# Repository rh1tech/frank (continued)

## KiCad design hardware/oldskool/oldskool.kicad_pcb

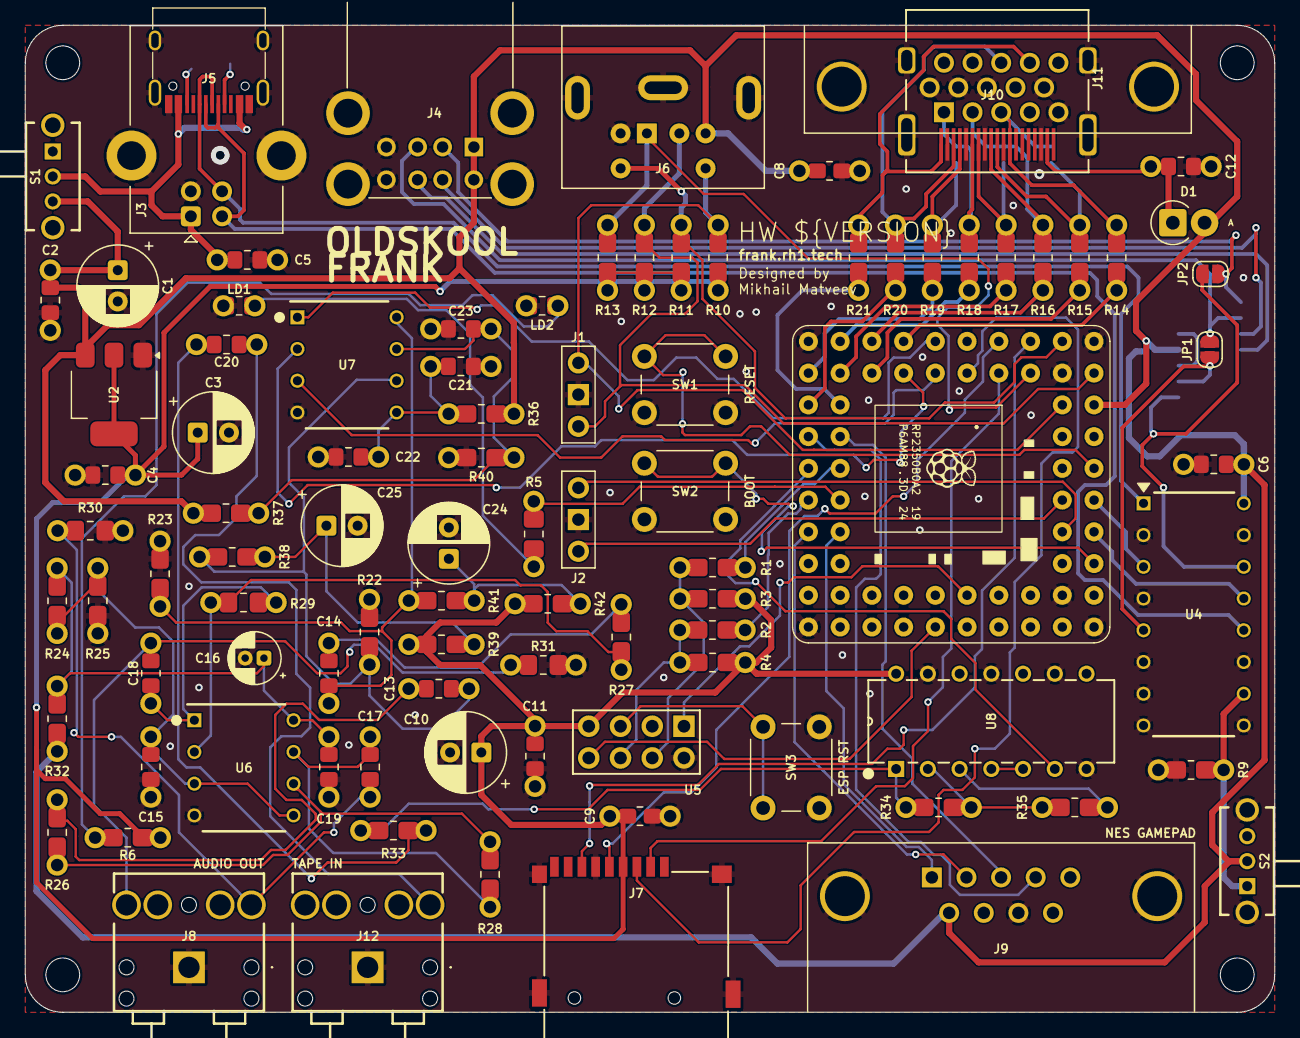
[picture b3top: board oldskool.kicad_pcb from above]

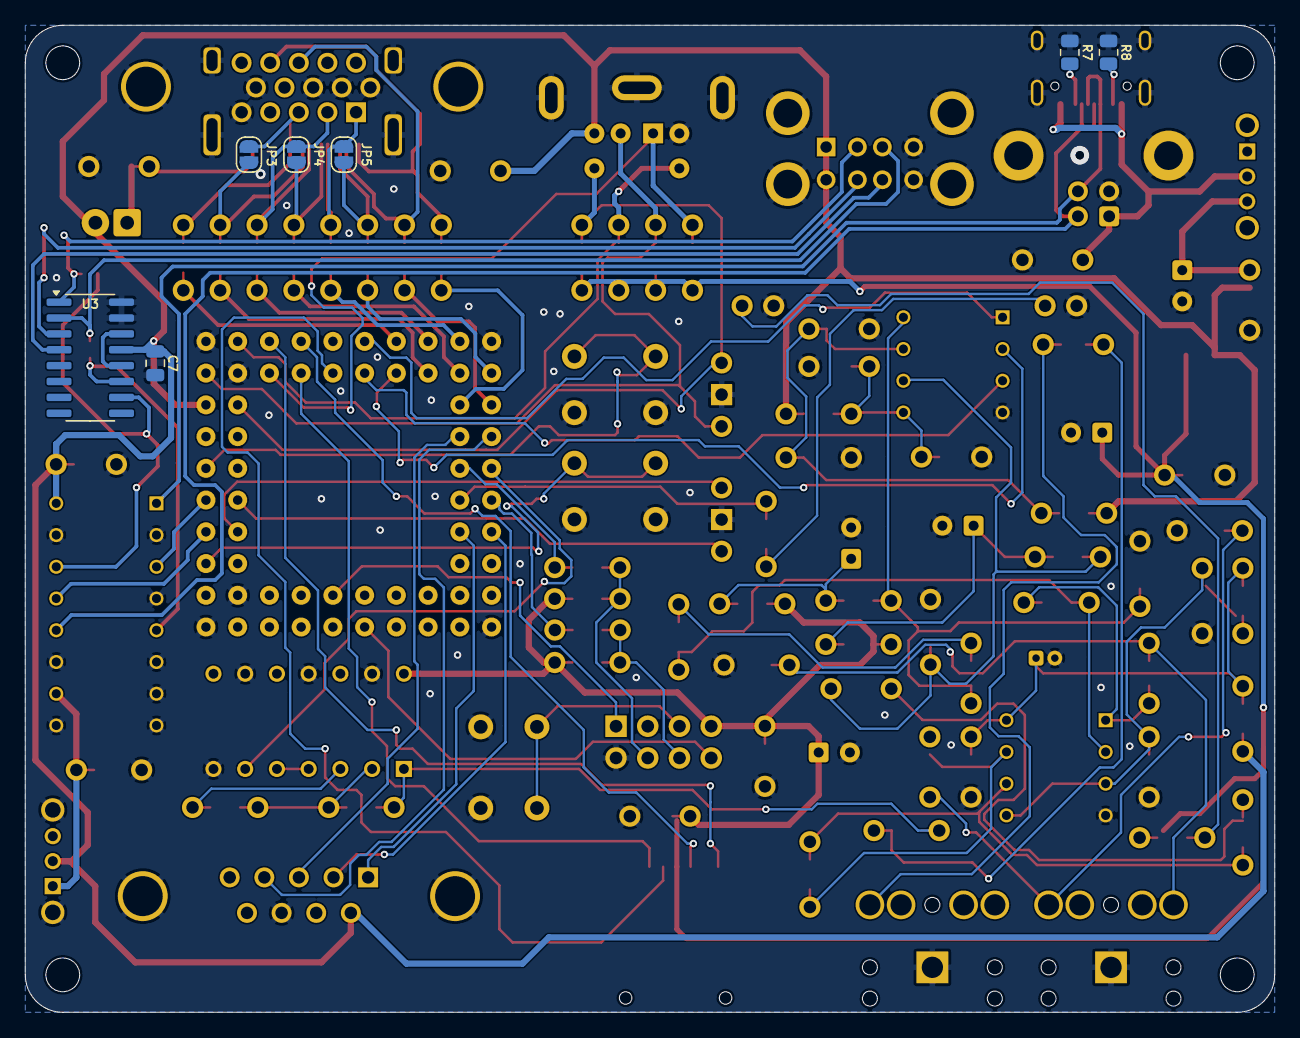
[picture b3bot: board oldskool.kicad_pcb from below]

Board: 2 copper layers, 100.0 x 79.0 mm, 104 parts (7 on the bottom side), 87 nets.

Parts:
C1, C3, C10, C24, C25: 100u; C_Radial_D6.3mm_P2.50mm
C2, C4, C6, C8, C9, C11, C12, C19, C20, C22: 100n; Combined_0805_CR
C5, C13, C14, C15, C17, C18, C21, C23: 10u; Combined_0805_CR
C7: 4.7u; C_0805_2012Metric
C16: 10u; CP_Radial_D4.0mm_P1.50mm
D1: 1N5819; D_SOD81_P2.54mm_Vertical_AnodeUp
H1, H2, H3, H4: Hole 2.7mm; MountingHole_2.7mm
J1: UART; PinSocket_1x03_P2.54mm_Vertical
J2: Debug; PinSocket_1x03_P2.54mm_Vertical
J3: USB_B; USB_B_Horizontal
J4: SS-52100-004; USB_A_Stacked
J5: USB4215-03-A; USB_C_Receptacle
J6: MDC-036; MiniDIN_6pin_Female
J7: 104031-0811; MicroSD_SMD_Long
J8: SJ1-3525N Green; AudioJack_3.5mm_SJ1-3525N_Green
J9: D-SUB 9 Male; DSUB-9_Male_TopMount
J10: DC3RX19JA2; HDMI_Female
J11: D-SUB 15 Female; DSUB-15_Female
J12: SJ1-3525N Red; AudioJack_3.5mm_SJ1-3525N_Red
JP1, JP2, JP3, JP4, JP5: Jumper (Solder); SolderJumper_2Pin
LD1: Blue; Combined_0805_LED
LD2: Green; Combined_0805_LED
R1, R2, R5, R6, R10, R11, R12, R13: 1K; Combined_0805_RE
R3, R4, R9, R24, R25, R26, R27, R40: 10K; Combined_0805_RE
R7, R8: 5.1K; R_0805_2012Metric
R14, R15, R16, R17, R18, R19, R20, R21: 220R; Combined_0805_RE
R22, R23: 2.2K; Combined_0805_RE
R28, R29: 47K; Combined_0805_RE
R30, R31: 20K; Combined_0805_RE
R32, R36, R39, R42: 100R; Combined_0805_RE
R33: 4.7K; Combined_0805_RE
R34, R35: 100K; Combined_0805_RE
R37: 51K; Combined_0805_RE
R38, R41: 470R; Combined_0805_RE
S1, S2: SK12D07VG3NS; Switch_Slide_SK12D07VG3NS
SW1: Reset; SW_PUSH_6mm_H5mm
SW2: Boot; SW_PUSH_6mm_H5mm
SW3: ESP01 Reset; SW_PUSH_6mm_H5mm
U1: Pimoroni PGA2350; PGA2350
U2: AMS1117-3.3; SOT-223-3_TabPin2
U3: MW7211A; SOP-16_3.9x9.9mm_P1.27mm
U4: 74HC4052; 74HC4052N
U5: ESP-01v090; ESP-01S
U6: LM358; DIP-8_W7.94mm_P2.54mm
U7: TDA1545A; DIP-8_W7.94mm_P2.54mm
U8: CD4069UBE

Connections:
+3V3: C3.1, C4.2, C9.2, C10.1, C11.2, J7.4 (VDD), R3.2, R4.2, R6.2, R10.2, R11.2, R12.2, R13.2, R39.1, R42.1, U2.2 (VO), U5.7 (VCC), U8.14 (VDD)
/Audio/AMP_OUTL: C17.2, J8.2 (TIP), R30.2
/Audio/AMP_OUTR: C18.2, J8.3 (RING), R31.2
/Audio/TDA_L: C13.1, R22.1, R38.2, U7.6 (IOL)
/Audio/TDA_R: C14.1, R23.1, R41.1, U7.8 (IOR)
/CDDAT3/GP5: J7.2 (DAT3/CD), U1.5 (GP5)
/CLKN/GP12: R14.2, U1.12 (GP12)
/CLKP/GP13: R15.2, U1.13 (GP13)
/CLK/GP6: J7.5 (CLK), U1.6 (GP6)
/CMD/GP7: J7.3 (CMD), U1.7 (GP7)
/D0N/GP14: R16.2, U1.14 (GP14)
/D0P/GP15: R17.2, U1.15 (GP15)
/D1N/GP16: R18.2, U1.16 (GP16)
/D1P/GP17: R19.2, U1.17 (GP17)
/D2N/GP18: R20.2, U1.19 (GP18)
/D2P/GP19: R21.2, U1.20 (GP19)
/DAT0/GP4: J7.7 (DAT0), U1.4 (GP4)
/DATA1/GP26: J9.2, U1.27 (GP26)
/DATA2/GP27: J9.1, U1.28 (GP27)
/DM: U1.53 (USB_DM), U4.13 (1Z)
/DP: U1.54 (USB_DP), U4.3 (2Z)
/EGP0/GP24: R2.2, U1.25 (GP24)
/EGP2/GP23: R1.2, U1.24 (GP23)
/ESP01S/GPIO0: R2.1, R4.1, U5.6 (GPIO0)
/ESP01S/GPIO2: R1.1, R3.1, U5.4 (GPIO2)
/J3/GP21: J9.3, U1.22 (GP21)
/J4/GP20: J9.4, U1.21 (GP20)
/KB_CLK/GP2: J6.5, R11.1, U1.2 (GP2)
/KB_DATA/GP3: J6.1, R13.1, U1.3 (GP3)
/LOAD_IN/GP22: U1.23 (GP22), U8.6 (I=*C)
/MS_CLK/GP0: J1.1, J6.6, R10.1, U1.61 (GP0)
/MS_DATA/GP1: J1.3, J6.2, R12.1, U1.62 (GP1)
/PGA2350/BOOTSEL: SW2.1, U1.51 (BOOTSEL)
/PGA2350/RUN: SW1.1, U1.56 (RUN)
/PGA2350/SWCLK: J2.3, U1.55 (SWCLK)
/PGA2350/SWDIO: J2.1, U1.52 (SWDIO)
/RX/GP38: U1.40 (GP38), U5.8 (URXD)
/TDA_DATA/GP9: U1.9 (GP9), U7.3 (DATA)
/TDA_LRCK/GP11: U1.11 (GP11), U7.2 (WS)
/TDA_SCLK/GP10: U1.10 (GP10), U7.1 (BCK)
/TX/GP39: U1.41 (GP39), U5.1 (UTXD)
/Tape In/TAPE: C20.2, J12.2 (TIP)
/USB/DI+: J3.3 (D+), J5.6 (DP1), J5.8 (DP2), U4.1 (2Y0)
/USB/DI-: J3.2 (D-), J5.5 (DN2), J5.7 (DN1), U4.12 (1Y0)
/USB/DS+: JP1.1 (A), U3.11 (DPU), U4.5 (2Y1)
/USB/DS-: JP2.1 (A), U3.10 (DMU), U4.14 (1Y1)
/USB/DU1+: J4.3 (D1+), JP1.2 (B), U3.2 (DP0)
/USB/DU1-: J4.2 (D1-), JP2.2 (B), U3.1 (DM0)
/USB/DU2+: J4.7 (D2+), U3.4 (DP1)
/USB/DU2-: J4.6 (D2-), U3.3 (DM1)
/USB/VBUS_IN: C5.1, J3.1 (VBUS), J5.2 (VBUS), J5.11 (VBUS), S1.2
/Video Out/VGA_B: J10.12 (CLKN), J11.3, JP3.1 (A), R14.1
/Video Out/VGA_BH: J10.10 (CLKP), JP3.2 (B), R15.1
/Video Out/VGA_G: J10.9 (D0N), J11.2, JP4.1 (A), R16.1
/Video Out/VGA_GH: J10.7 (D0P), JP4.2 (B), R17.1
/Video Out/VGA_HS: J10.3 (D2N), J11.13, R20.1
/Video Out/VGA_R: J10.6 (D1N), J11.1, JP5.1 (A), R18.1
/Video Out/VGA_RH: J10.4 (D1P), JP5.2 (B), R19.1
/Video Out/VGA_VS: J10.1 (D2P), J11.14, R21.1
GND: C1.2, C2.1, C3.2, C4.1, C5.2, C6.1, C7.2, C8.2, C9.1, C10.2, C11.1, C12.2, C15.1, C16.2, C19.1, C21.2, C22.2, C23.1, C24.2, C25.2, J1.2, J2.2, J3.4 (GND), J3.SH (Shield), J4.4 (GND1), J4.8 (GND2), J4.SH (Shield), J5.1 (GND), J5.12 (GND), J5.13 (SHIELD), J6.3, J7.6 (VSS), J8.1 (SLEEVE), J9.8, J10.2 (G_D2), J10.5 (G_D1), J10.8 (G_D0), J10.11 (G_CLK), J10.17 (G_DDC/CEC), J10.20 (SHIELD1), J10.21 (SHIELD2), J10.22 (SHIELD3), J10.23 (SHIELD4), J11.0, J11.5, J11.6, J11.7, J11.8, J11.10, J12.1 (SLEEVE), LD1.1 (K), LD2.1 (K), R7.1, R8.1, R9.1, R22.2, R23.2, R25.1, R30.1, R31.1, R40.1, S2.4 (MH1), S2.5 (MH2), SW1.2, SW2.2, SW3.2, U1.1 (GND), U1.18 (GND), U1.33 (GND), U1.48 (GND), U2.1 (GND), U3.15 (GND), U3.16 (GND), U4.2 (2Y2), U4.4 (2Y3), U4.6 (~E), U4.7 (VEE), U4.8 (GND), U4.9 (S1), U4.11 (1Y3), U4.15 (1Y2), U5.2 (GND), U6.4 (V-), U7.4 (GND), U8.7 (VSS), U8.9 (D14), U8.11 (E), U8.13 (F)
GP25: R5.2, U1.26 (GP25)
unnamed: C13.2, R26.2
unnamed: C14.2, R27.2
unnamed: C17.1, R28.1, U6.7
unnamed: C18.1, R29.1, U6.1
unnamed: C20.1, R33.2
unnamed: C24.1, R41.2, R42.2
unnamed: C25.1, R38.1, R39.2
unnamed: C12.1, D1.1 (K), J10.18 (+5V)
unnamed: J5.4 (CC1), R7.2
unnamed: J5.10 (CC2), R8.2
unnamed: LD1.2 (A), R5.1
unnamed: LD2.2 (A), R6.1
unnamed: U3.12 (VD33), U3.14 (VD3)
unnamed: R9.2, S2.1, U4.10 (S0)
unnamed: SW3.1, U5.5 (RST)
unnamed: C15.2, R24.1, R25.2, U6.3 (+), U6.5 (+)
unnamed: R27.1, R29.2, U6.2 (-)
unnamed: R26.1, R28.2, U6.6 (-)
unnamed: C16.1, C19.2, R24.2, R32.2, U6.8 (V+)
unnamed: C23.2, R37.2, R40.2, U7.7 (IREF)
unnamed: C21.1, C22.1, R36.1, U7.5 (VDD)
unnamed: R33.1, R34.2, U8.1 (A)
unnamed: R35.1, U8.3 (B)
unnamed: U8.4 (H=*B), U8.5 (C)
unnamed: R34.1, R35.2, U8.2 (G-*A)
VBUS: C1.1, C2.2, C6.2, C7.1, C8.1, D1.2 (A), J4.1 (VBUS1), J4.5 (VBUS2), J6.4, J9.6, R32.1, R36.2, R37.1, S1.3, S2.2, U1.60 (VBUS), U2.3 (VI), U3.13 (VDD5), U4.16 (VCC)

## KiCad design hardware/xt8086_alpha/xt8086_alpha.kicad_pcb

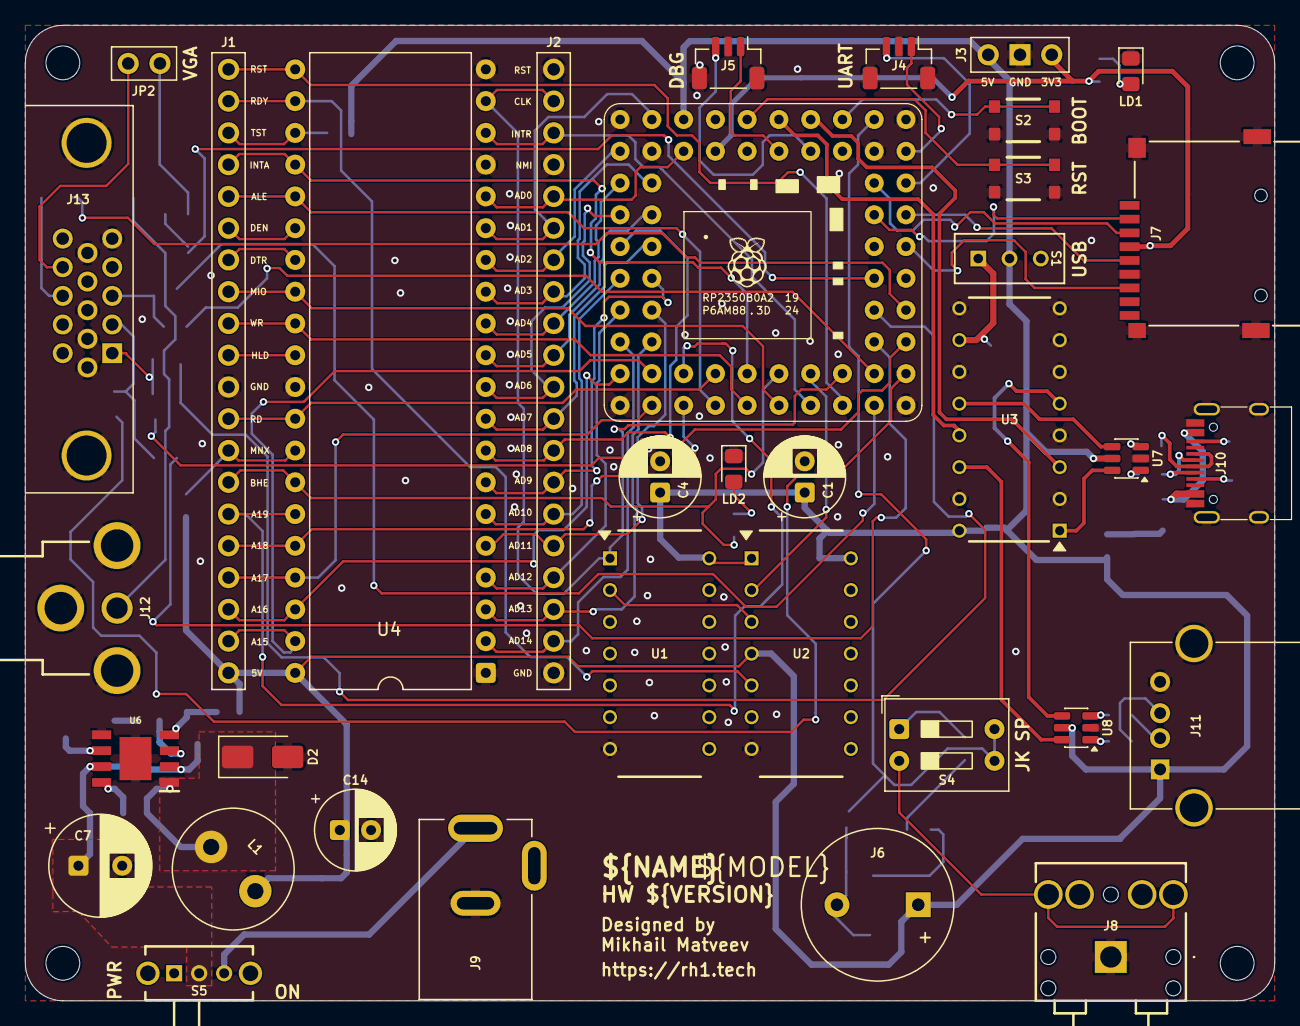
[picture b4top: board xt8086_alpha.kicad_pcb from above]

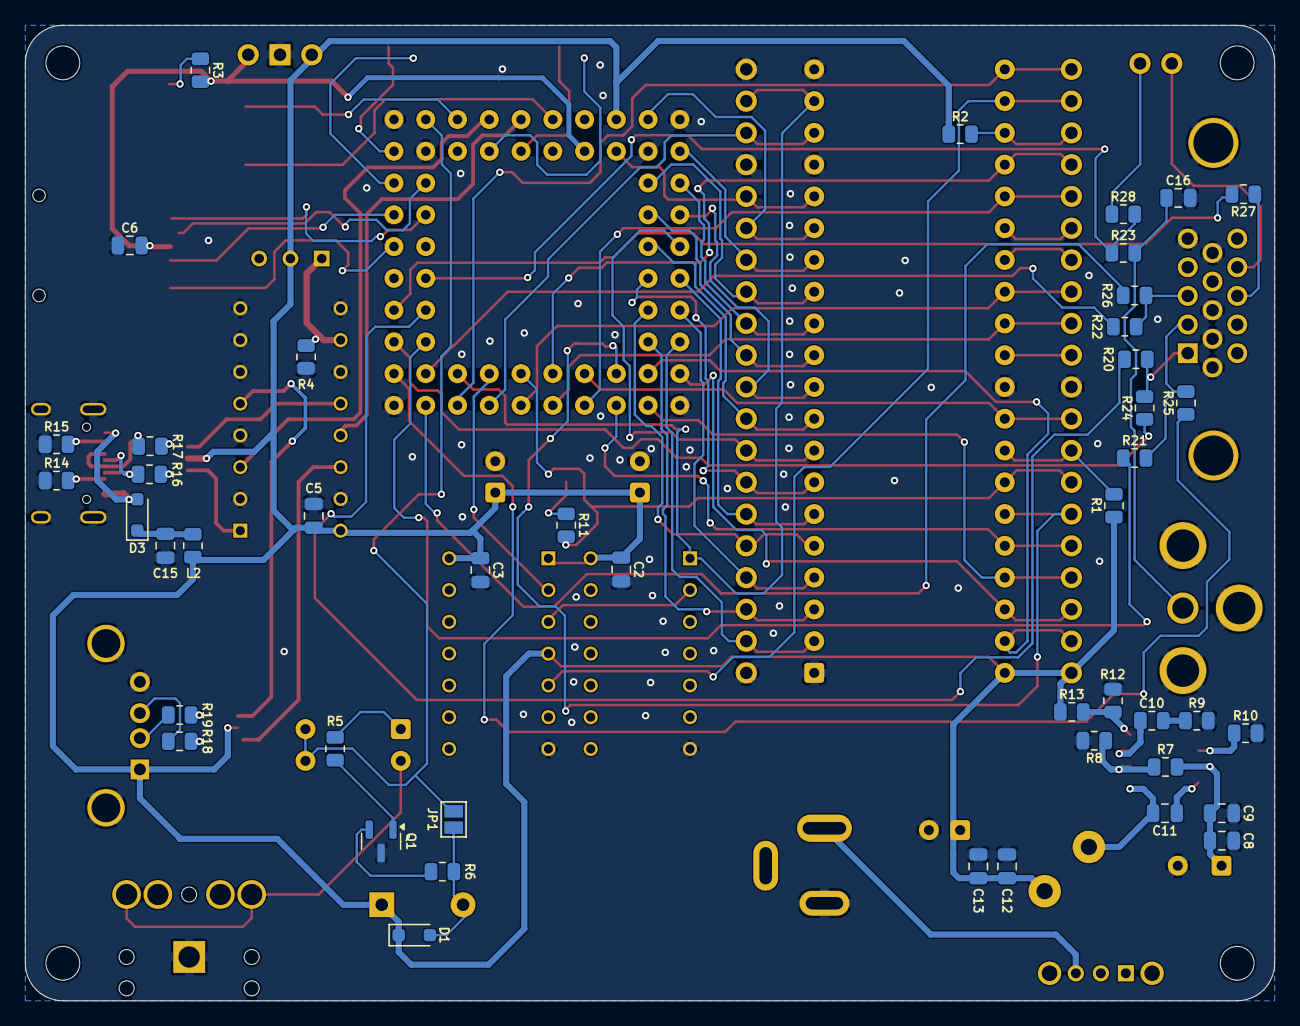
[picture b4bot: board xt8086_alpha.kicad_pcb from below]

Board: 2 copper layers, 99.9 x 78.0 mm, 84 parts (45 on the bottom side), 101 nets.

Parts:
C1, C4: 100u; CP_Radial_D6.3mm_P2.50mm
C2, C3, C5, C6, C9, C11, C12, C15: 100n; C_0805_2012Metric
C7: 680u; C_Radial_D8.0mm_P3.50mm
C8, C13: 10u; C_0805_2012Metric
C10: 150pF; R_0805_2012Metric
C14: 220u; C_Radial_D6.3mm_P2.50mm
C16: 470pF; C_0805_2012Metric
D1: 1N4148; D_SOD-323
D2: 1N5822; D_SMA
D3: 1N5819WS; D_SOD-323
H1, H2, H3, H4: Hole 2.7mm; MountingHole_2.7mm
J1: 8086_Pins_Left; PinSocket_1x20_P2.54mm_Vertical
J2: 8086_Pins_Right; PinSocket_1x20_P2.54mm_Vertical
J3: PWR; PinHeader_1x03_P2.54mm_Vertical
J4: UART; JST_SH_1x03_P1.00mm_Vertical
J5: Debug; JST_SH_1x03_P1.00mm_Vertical
J6: Buzzer; Buzzer_12x8.5RM6.5
J7: 104031-0811; MicroSD_SMD_Long
J8: SJ1-3525N; AudioJack_3.5mm_SJ1-3525N
J9: DC-005-5A-2.0; BarrelJack_DC-005
J10: USB4215-03-A; USB_C_Receptacle
J11: 676430910; USB_A_Single
J12: RCA-103; BarrelJack_RCJ-012
J13: D-SUB 15 Female; DSUB-15_Female
JP1: Direct; SolderJumper-2_P1.3mm_Open_Pad1.0x1.5mm
JP2: VGA VS; PinHeader_1x02_P2.54mm
L1: 22uH; L_Radial_D9.5mm_P5.00mm_Fastron_07HVP
L2: 330R; R_0805_2012Metric
LD1: Green; LED_0805_2012Metric_Pad1.15x1.40mm_HandSolder
LD2: Red; LED_0805_2012Metric_Pad1.15x1.40mm_HandSolder
Q1: BC847; SOT-23
R1, R2, R3, R5, R11, R24, R25, R26: 1K; R_0805_2012Metric
R4: 10K; R_0805_2012Metric
R6, R16, R17, R18, R19: 22R; R_0805_2012Metric
R7, R9, R10: 100K; R_0805_2012Metric
R8: 24K; R_0805_2012Metric
R12: 8.2K; R_0805_2012Metric
R13: 43K; R_0805_2012Metric
R14, R15: 5.1K; R_0805_2012Metric
R20, R21, R22: 330R; R_0805_2012Metric
R23: 75R; R_0805_2012Metric
R27, R28: 100R; R_0805_2012Metric
S1: SS12D00; Switch_Slide_SS12D00
S2: Boot; Button_SMD_3x4x2mm
S3: Reset; Button_SMD_3x4x2mm
S4: SW_DIP_x02; SW_DIP_SPSTx02_Slide_9.78x7.26mm_W7.62mm_P2.54mm
S5: SK12D07VG3NS; Switch_Slide_SK12D07VG3NS
U1: SN74LS04; DIP-14_W7.62mm
U2: SN74LS74; DIP-14_W7.62mm
U3: 74HC4052D; 74HC4052N
U4: 8086_Min_Mode; DIP-40_W15.24mm
U5: Pimoroni PGA2350; PGA2350
U6: MP1584EN-LF-Z; SOIC-9_P1.27mm
U7, U8: USBLC6-2SC6; SOT-23-6

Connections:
+3V3: C6.2, J3.3, J7.4 (VDD), R3.2, U5.59 (3V3)
/A16/GP16: J1.18, U4.38 (A16/S3), U5.16 (GP16)
/A17/GP17: J1.17, U4.37 (A17/S4), U5.17 (GP17)
/A18/GP18: J1.16, U4.36 (A18/S5), U5.19 (GP18)
/A19/GP19: J1.15, U4.35 (A19/S6), U5.20 (GP19)
/AD0/GP0: J2.5, U4.16 (AD0), U5.61 (GP0)
/AD1/GP1: J2.6, U4.15 (AD1), U5.62 (GP1)
/AD2/GP2: J2.7, U4.14 (AD2), U5.2 (GP2)
/AD3/GP3: J2.8, U4.13 (AD3), U5.3 (GP3)
/AD4/GP4: J2.9, U4.12 (AD4), U5.4 (GP4)
/AD5/GP5: J2.10, U4.11 (AD5), U5.5 (GP5)
/AD6/GP6: J2.11, U4.10 (AD6), U5.6 (GP6)
/AD7/GP7: J2.12, U4.9 (AD7), U5.7 (GP7)
/AD8/GP8: J2.13, U4.8 (AD8), U5.8 (GP8)
/AD9/GP9: J2.14, U4.7 (AD9), U5.9 (GP9)
/AD10/GP10: J2.15, U4.6 (AD10), U5.10 (GP10)
/AD11/GP11: J2.16, U4.5 (AD11), U5.11 (GP11)
/AD12/GP12: J2.17, U4.4 (AD12), U5.12 (GP12)
/AD13/GP13: J2.18, U4.3 (AD13), U5.13 (GP13)
/AD14/GP14: J2.19, U4.2 (AD14), U5.14 (GP14)
/AD15/GP15: J1.19, U4.39 (AD15), U5.15 (GP15)
/ALE/GP20: J1.5, U4.25 (ALE), U5.21 (GP20)
/Audio/JACK_IN: J8.2 (TIP), J8.3 (RING), S4.2
/Audio/SPEAKER: JP1.2, S4.3, S4.4, U5.49 (GP46)
/Audio/SPK_IN: R5.1, S4.1
/BOOTSEL: S2.2, S2.4, U5.51 (BOOTSEL)
/CLK/GP29: J2.2, U1.1 (1A), U4.19 (CLK), U5.30 (GP29)
/DEN: J1.6, U4.26 (~DEN)
/DT/R: J1.7, U4.27 (DT/~R)
/GP27: U2.2 (D1), U5.28 (GP27)
/HLDA: J1.10, U4.30 (HLDA)
/INTA/GP23: J1.4, U4.24 (~INTA), U5.24 (GP23)
/INTR/GP26: J2.3, U4.18 (INTR), U5.27 (GP26)
/MIO/GP24: J1.8, U4.28 (M/~IO), U5.25 (GP24)
/MN/MX: J1.13, R1.2, U4.33 (MN/~MX)
/Micro SD/CDDAT3: J7.2 (DAT3/CD), U5.43 (GP41)
/Micro SD/CLK: J7.5 (CLK), U5.44 (GP42)
/Micro SD/CMD: J7.3 (CMD), U5.45 (GP43)
/Micro SD/DAT0: J7.7 (DAT0), U5.42 (GP40)
/PGA2350/DM: U3.3 (2Z), U5.53 (USB_DM)
/PGA2350/DP: U3.13 (1Z), U5.54 (USB_DP)
/PGA2350/GP30: R26.1, U5.31 (GP30)
/PGA2350/GP31: R22.1, U5.32 (GP31)
/PGA2350/GP32: R25.1, U5.34 (GP32)
/PGA2350/GP33: R21.1, U5.35 (GP33)
/PGA2350/GP34: R24.1, U5.36 (GP34)
/PGA2350/GP35: R20.1, U5.37 (GP35)
/PGA2350/GP36: R27.2, U5.38 (GP36)
/PGA2350/GP37: R23.1, R28.2, U5.39 (GP37)
/Power/VBUS_IN: C7.1, C8.1, C9.1, R7.2, S5.2, U6.7 (VIN)
/RD/GP21: J1.12, U4.32 (~RD), U5.22 (GP21)
/READY: J1.2, U2.5 (Q1), U4.22 (READY)
/RESET/GP28: J1.1, U4.21 (RESET), U5.29 (GP28)
/RUN: S3.2, S3.4, U5.56 (RUN)
/SWCLK: J5.3, U5.55 (SWCLK)
/SWDIO: J5.1, U5.52 (SWDIO)
/TEST: J1.3, R2.2, U4.23 (~TEST)
/UART0_RX: J4.3, U5.47 (GP45)
/UART0_TX: J4.1, U5.46 (GP44)
/USB/SW: R4.2, S1.1, U3.10 (S0)
/USB/UAM: U3.5 (2Y1), U8.4 (I/O2)
/USB/UAP: U3.14 (1Y1), U8.6 (I/O1)
/USB/UCM: U3.1 (2Y0), U7.6 (I/O1)
/USB/UCP: U3.12 (1Y0), U7.4 (I/O2)
/USB/VBUS_IN: C15.1, D3.1 (K), L2.2
/WR/GP22: J1.9, U4.29 (~WR), U5.23 (GP22)
GND: C1.2, C2.2, C3.2, C4.2, C5.1, C6.1, C7.2, C8.2, C9.2, C12.1, C13.2, C14.2, C15.2, C16.2, D2.2 (A), J1.11, J2.1, J2.4, J2.20, J3.2, J4.2, J5.2, J7.6 (VSS), J7.SH (SHIELD), J8.1 (SLEEVE), J9.2, J10.1 (GND), J10.12 (GND), J10.13 (SHIELD), J11.4 (GND), J11.5 (Shield), J12.2, J13.0, J13.5, J13.6, J13.7, J13.8, J13.10, LD1.1 (K), LD2.1 (K), Q1.3 (E), R4.1, R8.2, R9.2, R10.2, R12.1, R14.1, R15.1, S2.1, S2.3, S3.1, S3.3, U1.7 (GND), U2.7 (GND), U3.2 (2Y2), U3.4 (2Y3), U3.6 (~E), U3.7 (VEE), U3.8 (GND), U3.9 (S1), U3.11 (1Y3), U3.15 (1Y2), U4.1 (GND), U4.17 (NMI), U4.20 (GND), U4.31 (HOLD), U5.1 (GND), U5.18 (GND), U5.33 (GND), U5.48 (GND), U6.5 (GND), U6.9 (EP), U7.2 (GND), U8.2 (GND)
GP25: J1.14, R11.2, U4.34 (~BHE/S7), U5.26 (GP25)
unnamed: C10.2, R9.1
unnamed: D1.2 (A), J6.2 (-), JP1.1, R6.1
unnamed: C11.2, D2.1 (K), L1.1, U6.1 (SW)
unnamed: D3.2 (A), J10.2 (VBUS), J10.11 (VBUS)
unnamed: J9.1, S5.3
unnamed: J10.4 (CC1), R14.2
unnamed: J10.10 (CC2), R15.2
unnamed: J10.5 (DN2), J10.7 (DN1), R16.2
unnamed: J10.6 (DP1), J10.8 (DP2), R17.2
unnamed: J11.3 (D+), R18.2
unnamed: J11.2 (D-), R19.2
unnamed: C16.1, J12.1, R23.2
unnamed: J13.1, R20.2, R24.2
unnamed: J13.2, R21.2, R25.2
unnamed: J13.3, R22.2, R26.2
unnamed: J13.13, R27.1
unnamed: J13.14, JP2.1
unnamed: JP2.2, R28.1
unnamed: LD1.2 (A), R3.1
unnamed: LD2.2 (A), R11.1
unnamed: Q1.2 (B), R5.2
unnamed: Q1.1 (C), R6.2
unnamed: R16.1, U7.1 (I/O1)
unnamed: R17.1, U7.3 (I/O2)
unnamed: R18.1, U8.1 (I/O1)
unnamed: R19.1, U8.3 (I/O2)
unnamed: U1.2 (1Y), U2.3 (CLK1)
unnamed: C11.1, U6.8 (BST)
unnamed: C10.1, U6.3 (COMP)
unnamed: R7.1, R8.1, U6.2 (EN)
unnamed: R12.2, R13.2, U6.4 (FB)
unnamed: R10.1, U6.6 (FREQ)
VBUS: C1.1, C2.1, C3.1, C4.1, C5.2, C12.2, C13.1, C14.1, D1.1 (K), J1.20, J3.1, J6.1 (+), J11.1 (VBUS), L1.2, L2.1, R1.1, R2.1, R13.1, S1.2, U1.14 (VCC), U2.1 (CLR1), U2.4 (PR1), U2.14 (VCC), U3.16 (VCC), U4.40 (VCC), U5.60 (VBUS), U7.5 (VBUS), U8.5 (VBUS)

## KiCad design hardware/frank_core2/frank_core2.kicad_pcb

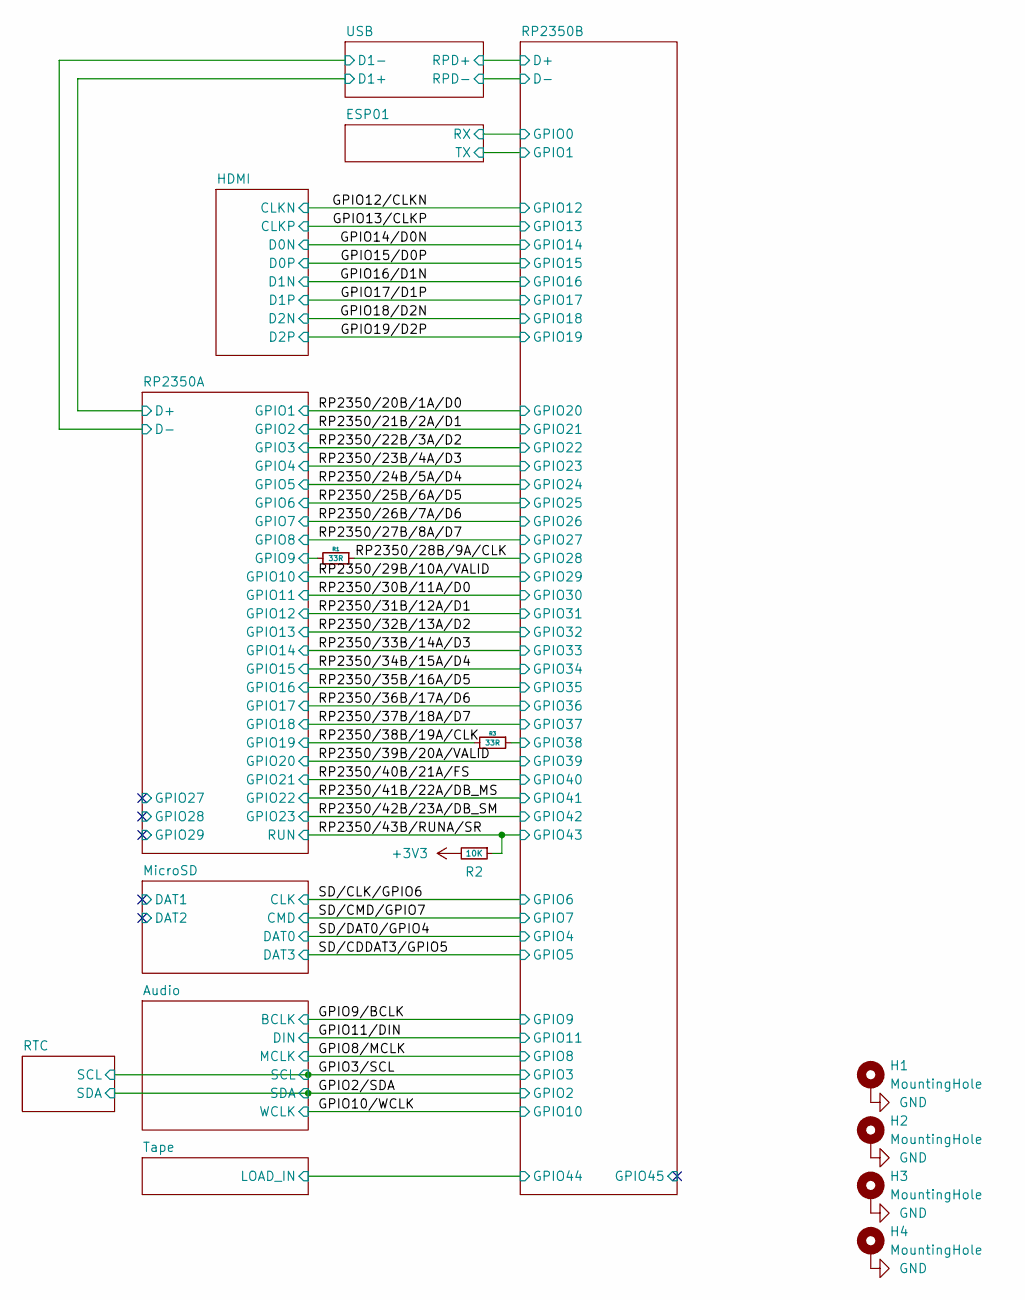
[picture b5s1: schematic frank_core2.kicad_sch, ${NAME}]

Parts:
H1, H2, H3, H4: MountingHole; MountingHole_2.5mm_Pad_Via
R1, R3: 33R; R_0603_1608Metric; LCSC C23140
R2: 10K; R_0603_1608Metric; LCSC C2906982

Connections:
+3V3: R2.2; also elsewhere on the board
/RP2350A/GPIO9: R1.2; also elsewhere on the board
/RP2350B/GPIO38: R3.1; also elsewhere on the board
/RP2350/28B/9A/CLK: R1.1; also elsewhere on the board
/RP2350/38B/19A/CLK: R3.2; also elsewhere on the board
/RP2350/43B/RUNA/SR: R2.1; also elsewhere on the board
GND: H1.1 (1_1), H2.1 (1_1), H3.1 (1_1), H4.1 (1_1); also elsewhere on the board

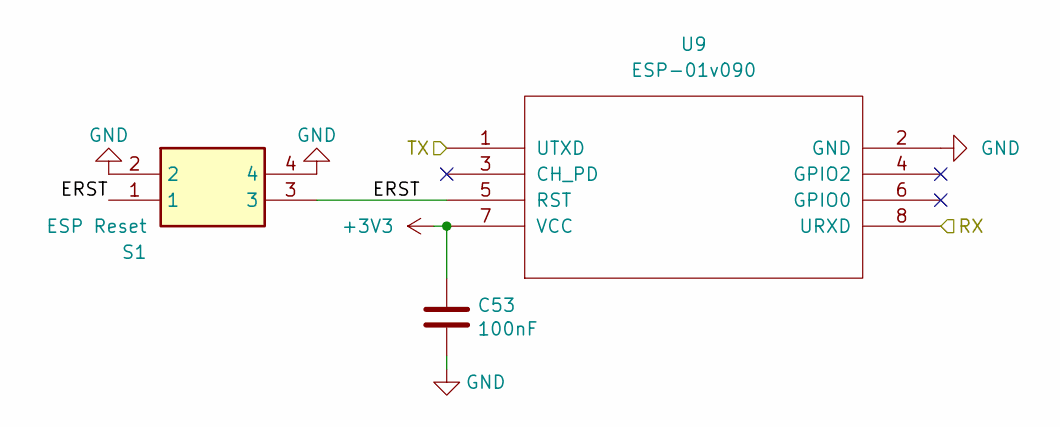
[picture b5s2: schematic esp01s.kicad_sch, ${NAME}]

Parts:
C53: 100nF; C_0603_1608Metric; LCSC C14663
S1: ESP Reset; Button_SMD_3x4x2mm; Mouser Part Number 611-KMR221G-LFS; LCSC C36498961
U9: ESP-01v090; ESP-01

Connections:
+3V3: C53.1, U9.7 (VCC); also elsewhere on the board
/ESP01/ERST: S1.1, S1.3, U9.5 (RST)
/ESP01/RX: U9.8 (URXD); also elsewhere on the board
/ESP01/TX: U9.1 (UTXD); also elsewhere on the board
GND: C53.2, S1.2, S1.4, U9.2 (GND); also elsewhere on the board

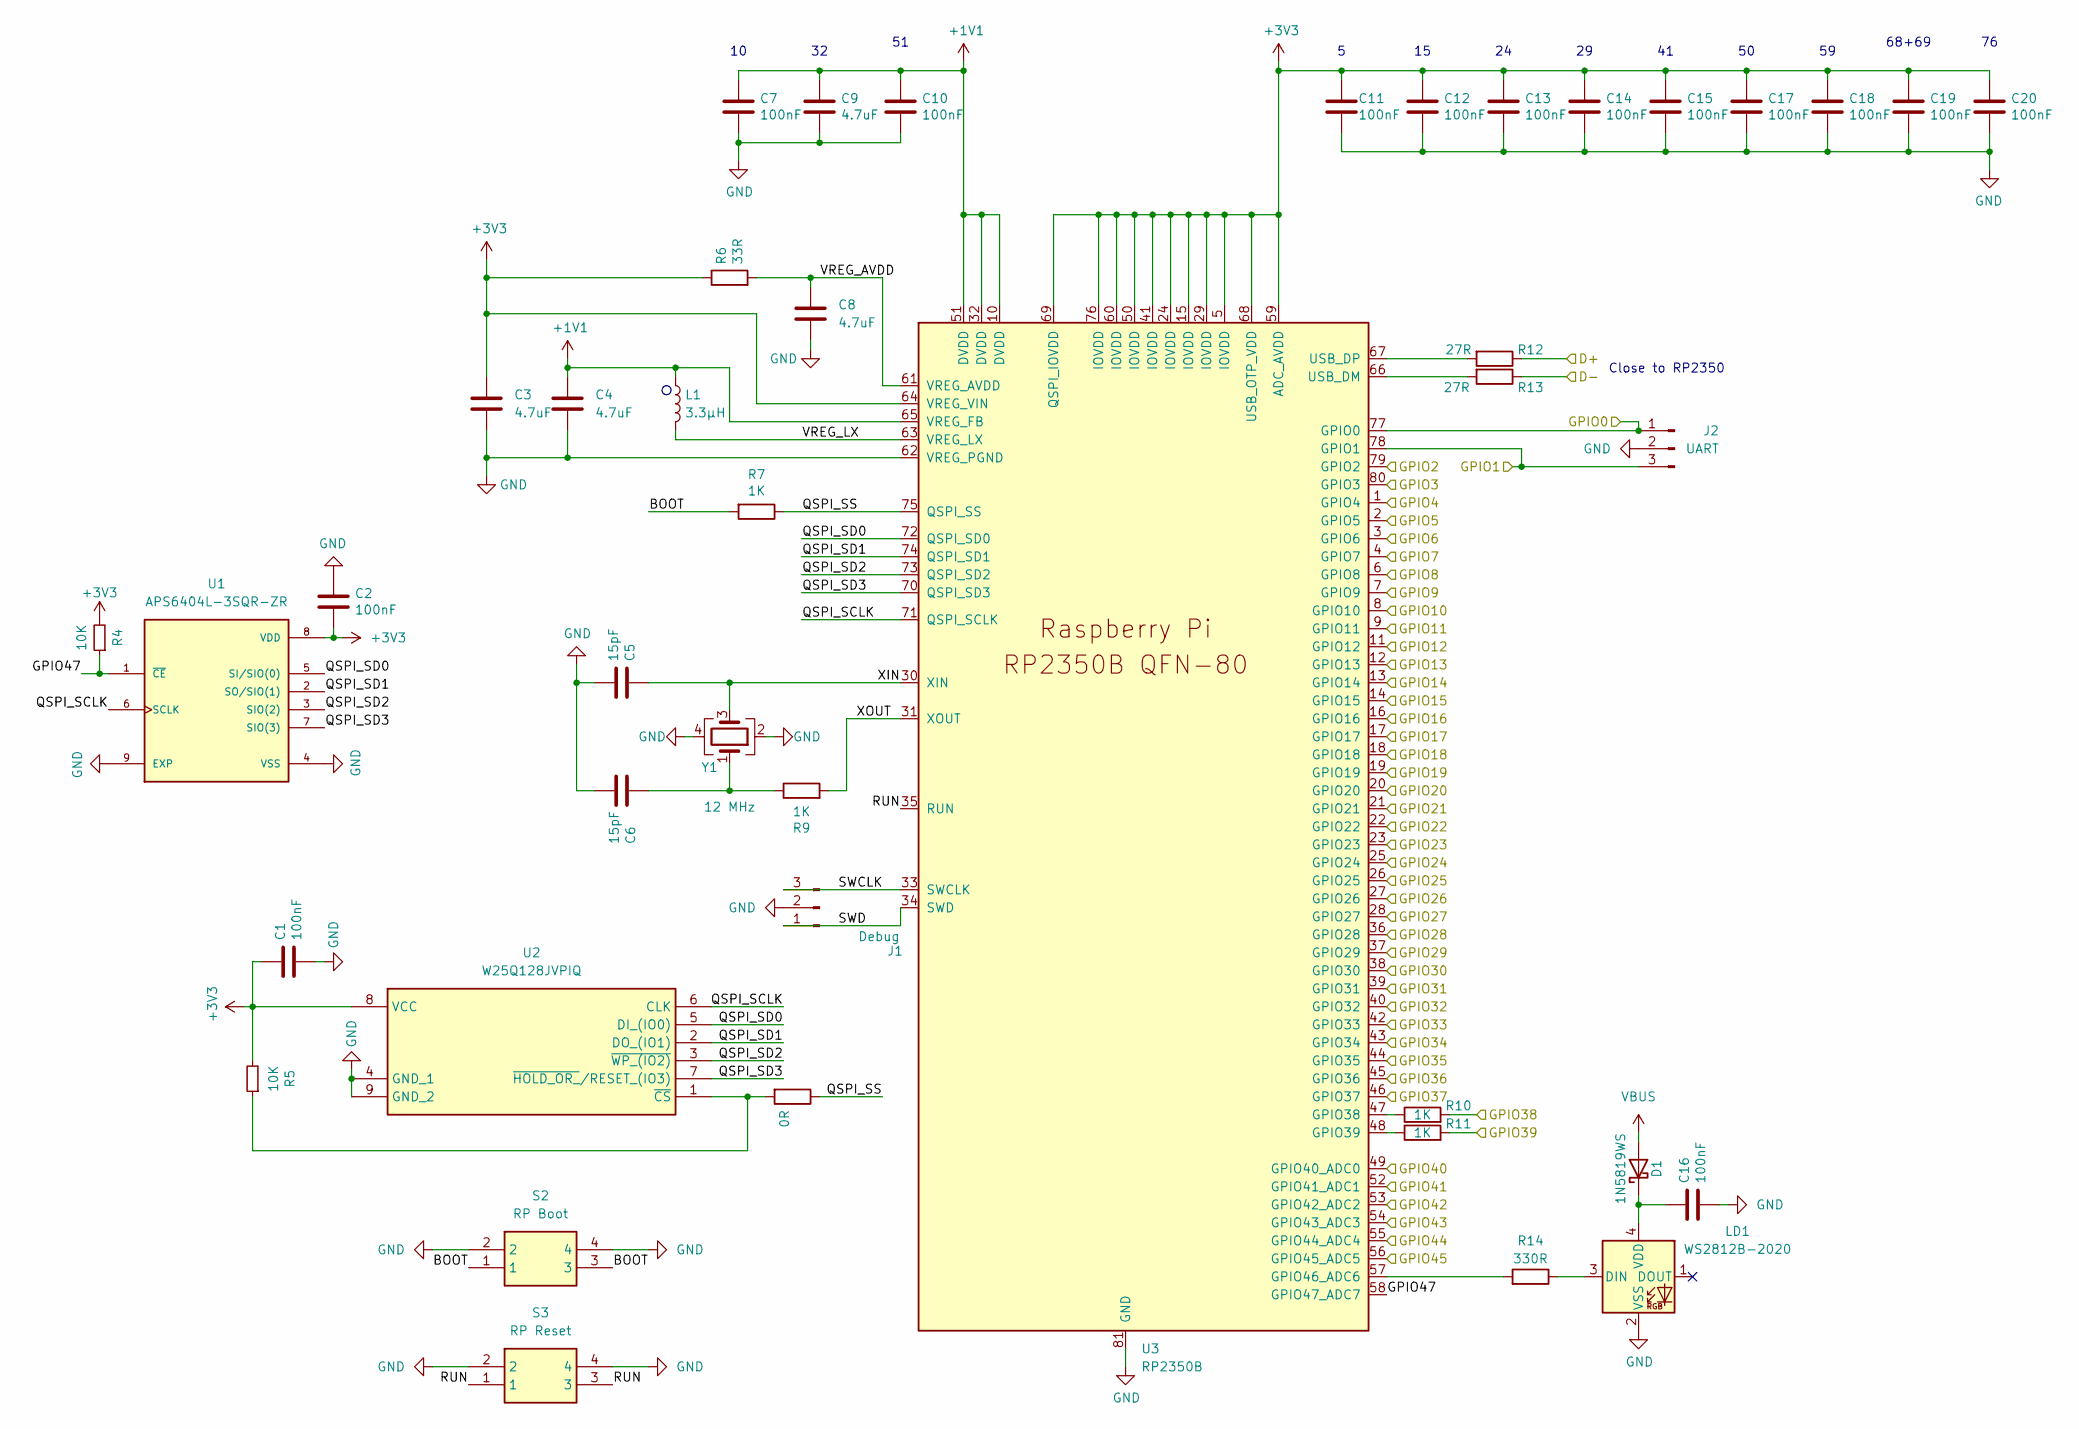
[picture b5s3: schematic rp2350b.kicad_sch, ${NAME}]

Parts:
C1, C2, C7, C10, C11, C12, C13, C14, C15, C16, C17, C18, C19, C20: 100nF; C_0603_1608Metric; LCSC C14663
C3, C4, C8, C9: 4.7uF; C_0603_1608Metric; LCSC C5360844
C5, C6: 15pF; C_0603_1608Metric; LCSC C1644
D1: 1N5819WS; D_SOD-323; LCSC C191023
J1: Debug; JST_SH_1x03_P1.00mm_Vertical; LCSC C160389
J2: UART; JST_SH_1x03_P1.00mm_Vertical; LCSC C160389
L1: 3.3µH; L_AOTA-B201610_2.0x1.6mm; LCSC C98035
LD1: WS2812B-2020; LED_WS2812B-2020_PLCC4_2.0x2.0mm; LCSC C965555
R4, R5: 10K; R_0603_1608Metric; LCSC C2906982
R6: 33R; R_0603_1608Metric; LCSC C23140
R7, R9, R10, R11: 1K; R_0603_1608Metric; LCSC C21190
R8: 0R; R_0603_1608Metric; LCSC C21189
R12, R13: 27R; R_0603_1608Metric; LCSC C25190
R14: 330R; R_0603_1608Metric; LCSC C23138
S2: RP Boot; Button_SMD_3x4x2mm; Mouser Part Number 611-KMR221G-LFS; LCSC C36498961
S3: RP Reset; Button_SMD_3x4x2mm; Mouser Part Number 611-KMR221G-LFS; LCSC C36498961
U1: APS6404L-3SQR-ZR; PSON50P200X300X50-9N; PARTREV 2.3; LCSC C3040877
U2: W25Q128JVPIQ; WSON-8-1EP_6x5mm_P1.27mm_EP3.45x4.35mm; Mouser Part Number 454-W25Q128JVPIQ; LCSC C190862
U3: RP2350B; RP2350-QFN-80_10x10_P0.4mm; LCSC C42415655
Y1: 12 MHz; Crystal_SMD_3225-4Pin_3.2x2.5mm; LCSC C9002

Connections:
+1V1: C4.1, C7.1, C9.1, C10.1, L1.1, U3.10 (DVDD), U3.32 (DVDD), U3.51 (DVDD), U3.65 (VREG_FB)
+3V3: C1.1, C2.2, C3.1, C11.1, C12.1, C13.1, C14.1, C15.1, C17.1, C18.1, C19.1, C20.1, R4.2, R5.2, R6.1, U1.8 (VDD), U2.8 (VCC), U3.5 (IOVDD), U3.15 (IOVDD), U3.24 (IOVDD), U3.29 (IOVDD), U3.41 (IOVDD), U3.50 (IOVDD), U3.59 (ADC_AVDD), U3.60 (IOVDD), U3.64 (VREG_VIN), U3.68 (USB_OTP_VDD), U3.69 (QSPI_IOVDD), U3.76 (IOVDD); also elsewhere on the board
/ESP01/RX: J2.1, U3.77 (GPIO0); also elsewhere on the board
/ESP01/TX: J2.3, U3.78 (GPIO1); also elsewhere on the board
/GPIO2/SDA: U3.79 (GPIO2); also elsewhere on the board
/GPIO3/SCL: U3.80 (GPIO3); also elsewhere on the board
/GPIO8/MCLK: U3.6 (GPIO8); also elsewhere on the board
/GPIO9/BCLK: U3.7 (GPIO9); also elsewhere on the board
/GPIO10/WCLK: U3.8 (GPIO10); also elsewhere on the board
/GPIO11/DIN: U3.9 (GPIO11); also elsewhere on the board
/GPIO12/CLKN: U3.11 (GPIO12); also elsewhere on the board
/GPIO13/CLKP: U3.12 (GPIO13); also elsewhere on the board
/GPIO14/D0N: U3.13 (GPIO14); also elsewhere on the board
/GPIO15/D0P: U3.14 (GPIO15); also elsewhere on the board
/GPIO16/D1N: U3.16 (GPIO16); also elsewhere on the board
/GPIO17/D1P: U3.17 (GPIO17); also elsewhere on the board
/GPIO18/D2N: U3.18 (GPIO18); also elsewhere on the board
/GPIO19/D2P: U3.19 (GPIO19); also elsewhere on the board
/RP2350B/BOOT: R7.2, S2.1, S2.3
/RP2350B/D+: R12.1; also elsewhere on the board
/RP2350B/D-: R13.1; also elsewhere on the board
/RP2350B/GPIO38: R10.2; also elsewhere on the board
/RP2350B/GPIO44: U3.55 (GPIO44_ADC4); also elsewhere on the board
/RP2350B/GPIO45: U3.56 (GPIO45_ADC5)
/RP2350B/GPIO47: R4.1, U1.1 (~CE), U3.58 (GPIO47_ADC7)
/RP2350B/QSPI_SCLK: U1.6 (SCLK), U2.6 (CLK), U3.71 (QSPI_SCLK)
/RP2350B/QSPI_SD0: U1.5 (SI/SIO(0)), U2.5 (DI_(IO0)), U3.72 (QSPI_SD0)
/RP2350B/QSPI_SD1: U1.2 (SO/SIO(1)), U2.2 (DO_(IO1)), U3.74 (QSPI_SD1)
/RP2350B/QSPI_SD2: U1.3 (SIO(2)), U2.3 (~WP_(IO2)), U3.73 (QSPI_SD2)
/RP2350B/QSPI_SD3: U1.7 (SIO(3)), U2.7 (~HOLD_OR_/RESET_(IO3)), U3.70 (QSPI_SD3)
/RP2350B/QSPI_SS: R7.1, R8.1, U3.75 (QSPI_SS)
/RP2350B/RUN: S3.1, S3.3, U3.35 (RUN)
/RP2350B/SWCLK: J1.3, U3.33 (SWCLK)
/RP2350B/SWD: J1.1, U3.34 (SWD)
/RP2350B/VREG_AVDD: C8.1, R6.2, U3.61 (VREG_AVDD)
/RP2350B/VREG_LX: L1.2, U3.63 (VREG_LX)
/RP2350B/XIN: C5.1, U3.30 (XIN), Y1.3
/RP2350B/XOUT: R9.2, U3.31 (XOUT)
/RP2350/20B/1A/D0: U3.20 (GPIO20); also elsewhere on the board
/RP2350/21B/2A/D1: U3.21 (GPIO21); also elsewhere on the board
/RP2350/22B/3A/D2: U3.22 (GPIO22); also elsewhere on the board
/RP2350/23B/4A/D3: U3.23 (GPIO23); also elsewhere on the board
/RP2350/24B/5A/D4: U3.25 (GPIO24); also elsewhere on the board
/RP2350/25B/6A/D5: U3.26 (GPIO25); also elsewhere on the board
/RP2350/26B/7A/D6: U3.27 (GPIO26); also elsewhere on the board
/RP2350/27B/8A/D7: U3.28 (GPIO27); also elsewhere on the board
/RP2350/28B/9A/CLK: U3.36 (GPIO28); also elsewhere on the board
/RP2350/29B/10A/VALID: U3.37 (GPIO29); also elsewhere on the board
/RP2350/30B/11A/D0: U3.38 (GPIO30); also elsewhere on the board
/RP2350/31B/12A/D1: U3.39 (GPIO31); also elsewhere on the board
/RP2350/32B/13A/D2: U3.40 (GPIO32); also elsewhere on the board
/RP2350/33B/14A/D3: U3.42 (GPIO33); also elsewhere on the board
/RP2350/34B/15A/D4: U3.43 (GPIO34); also elsewhere on the board
/RP2350/35B/16A/D5: U3.44 (GPIO35); also elsewhere on the board
/RP2350/36B/17A/D6: U3.45 (GPIO36); also elsewhere on the board
/RP2350/37B/18A/D7: U3.46 (GPIO37); also elsewhere on the board
/RP2350/39B/20A/VALID: R11.2; also elsewhere on the board
/RP2350/40B/21A/FS: U3.49 (GPIO40_ADC0); also elsewhere on the board
/RP2350/41B/22A/DB_MS: U3.52 (GPIO41_ADC1); also elsewhere on the board
/RP2350/42B/23A/DB_SM: U3.53 (GPIO42_ADC2); also elsewhere on the board
/RP2350/43B/RUNA/SR: U3.54 (GPIO43_ADC3); also elsewhere on the board
/SD/CDDAT3/GPIO5: U3.2 (GPIO5); also elsewhere on the board
/SD/CLK/GPIO6: U3.3 (GPIO6); also elsewhere on the board
/SD/CMD/GPIO7: U3.4 (GPIO7); also elsewhere on the board
/SD/DAT0/GPIO4: U3.1 (GPIO4); also elsewhere on the board
GND: C1.2, C2.1, C3.2, C4.2, C5.2, C6.2, C7.2, C8.2, C9.2, C10.2, C11.2, C12.2, C13.2, C14.2, C15.2, C16.2, C17.2, C18.2, C19.2, C20.2, J1.2, J2.2, LD1.2 (VSS), S2.2, S2.4, S3.2, S3.4, U1.4 (VSS), U1.9 (EXP), U2.4 (GND_1), U2.9 (GND_2), U3.62 (VREG_PGND), U3.81 (GND), Y1.2, Y1.4; also elsewhere on the board
unnamed: C6.1, R9.1, Y1.1
unnamed: C16.1, D1.1 (K), LD1.4 (VDD)
unnamed: LD1.3 (DIN), R14.1
unnamed: R5.1, R8.2, U2.1 (~CS)
unnamed: R10.1, U3.47 (GPIO38)
unnamed: R11.1, U3.48 (GPIO39)
unnamed: R14.2, U3.57 (GPIO46_ADC6)
unnamed: R13.2, U3.66 (USB_DM)
unnamed: R12.2, U3.67 (USB_DP)
VBUS: D1.2 (A); also elsewhere on the board

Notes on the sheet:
Close to RP2350
68+69
